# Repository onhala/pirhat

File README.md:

# PIR Sensor Adaption Board

This repository focuses on the development of an adaptation board for the PIR sensor HC-SR501, intended for use in home automation projects. The board adapts the PIR module for integration into a 24V control system.

## Schematic and PCB

The schematic and PCB are located in the `schmatic_pcb` folder in KiCad format.
You can view the schematic online using KiCanvas: [View Schematic](https://kicanvas.org/?github=https%3A%2F%2Fgithub.com%2Fonhala%2Fpirhat%2Ftree%2Fmain%2Fschematic_pcb)

## Cover Manufacturing Files

The manufacturing files for the plastic cover are located in the `cover` folder. They are available in both DWG and PDF formats.

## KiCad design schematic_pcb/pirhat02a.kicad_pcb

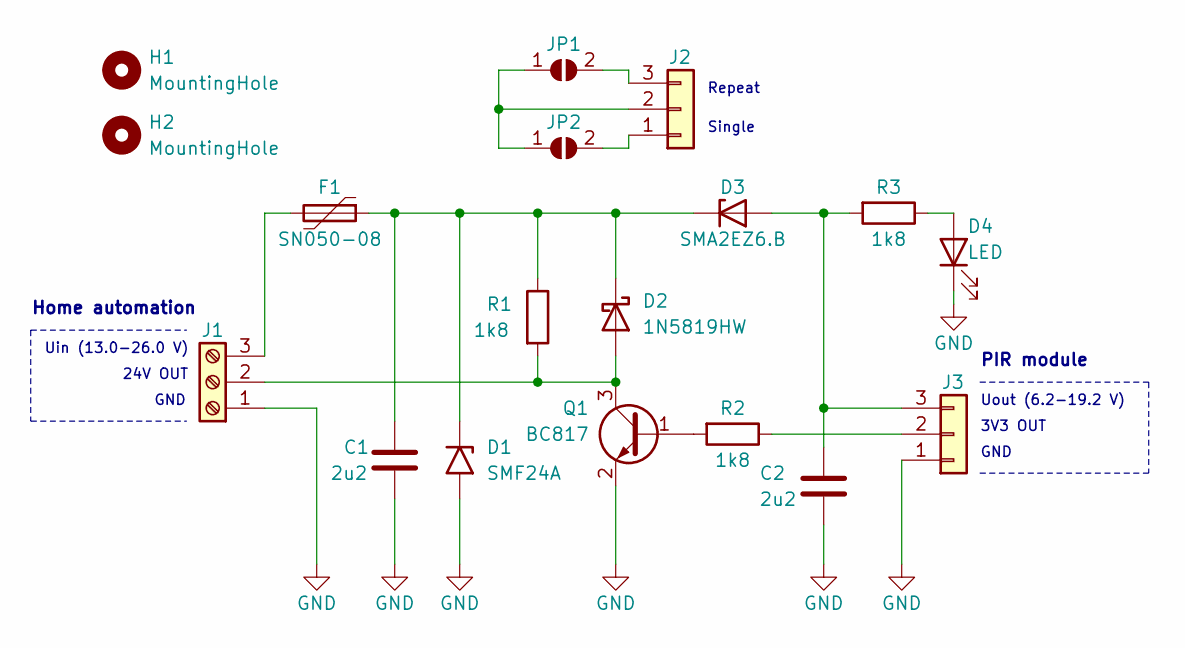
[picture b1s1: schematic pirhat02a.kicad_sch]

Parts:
C1, C2: 2u2; C_1206_3216Metric
D1: SMF24A; D_SMF
D2: 1N5819HW; D_SOD-123
D3: SMA2EZ6.B; D_SMA_Handsoldering
D4: LED; LED_1206_3216Metric_Pad1.42x1.75mm_HandSolder
F1: SN050-08; R_1206_3216Metric_Pad1.30x1.75mm_HandSolder
H1, H2: MountingHole; MountingHole_2.2mm_M2
J1: Screw_Terminal_01x03; TerminalBlock_Phoenix_MKDS-1,5-3-5.08_1x03_P5.08mm_Horizont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
J2, J3: Conn_01x03; PinHeader_1x03_P2.54mm_Vertical
JP1, JP2: SolderJumper_2_Open; SolderJumper-2_P1.3mm_Open_TrianglePad1.0x1.5mm
Q1: BC817; SOT-23_Handsoldering
R1, R2, R3: 1k8; R_1206_3216Metric_Pad1.30x1.75mm_HandSolder

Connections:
GND: C1.2, C2.2, D1.2 (A2), D4.1 (K), J1.1, J3.1, Q1.2 (E)
unnamed: C1.1, D1.1 (A1), D2.1 (K), D3.1 (K), F1.1, R1.1
unnamed: D2.2 (A), J1.2, Q1.3 (C), R1.2
unnamed: C2.1, D3.2 (A), J3.3, R3.2
unnamed: D4.2 (A), R3.1
unnamed: F1.2, J1.3
unnamed: J2.1, JP2.2 (B)
unnamed: J2.2, JP1.1 (A), JP2.1 (A)
unnamed: J2.3, JP1.2 (B)
unnamed: J3.2, R2.1
unnamed: Q1.1 (B), R2.2

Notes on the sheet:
Single
GND
24V OUT
Uout (6.2-19.2 V)
Repeat
Uin (13.0-26.0 V)
PIR module
GND
Home automation
3V3 OUT

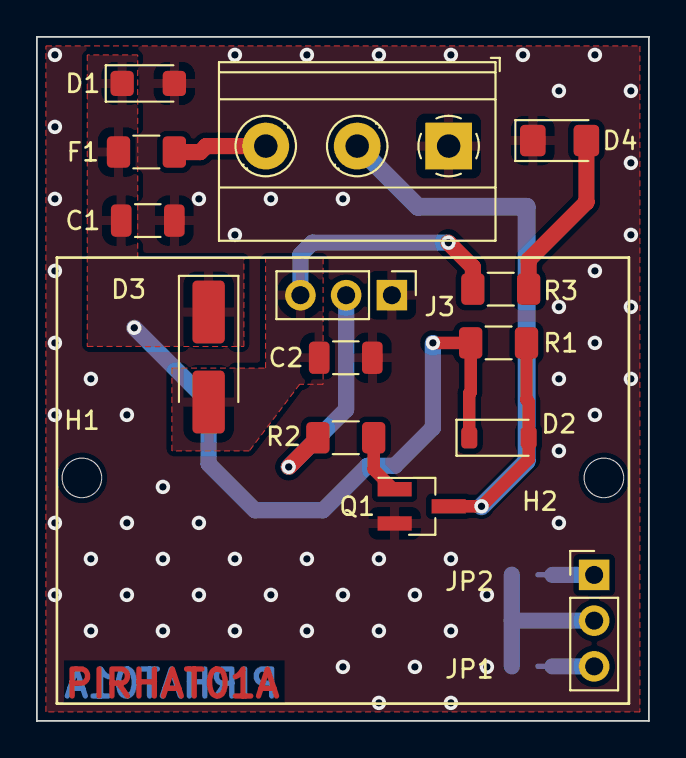
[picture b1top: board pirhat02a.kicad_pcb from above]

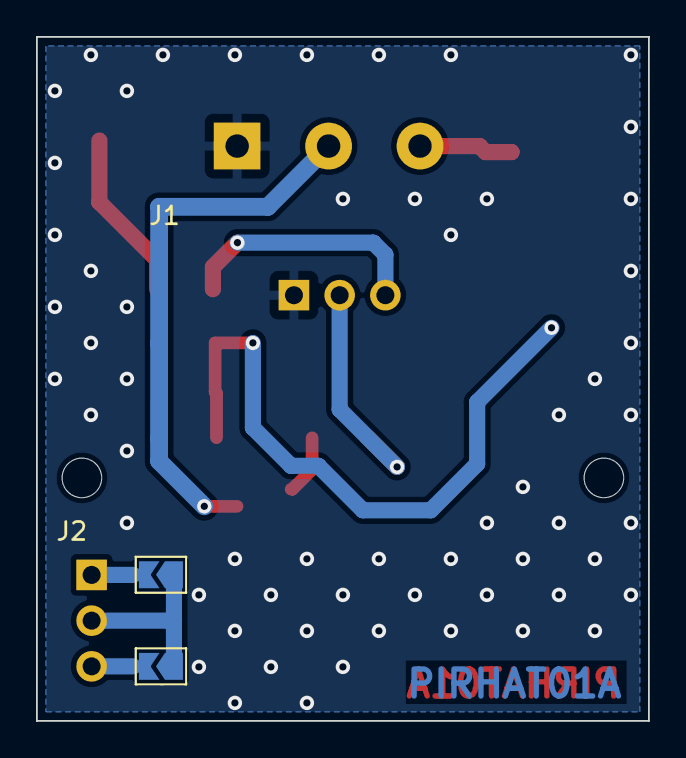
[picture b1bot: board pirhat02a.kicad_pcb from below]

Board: 2 copper layers, 34.0 x 38.0 mm, 18 parts (2 on the bottom side), 11 nets.

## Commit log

2024-12-05 Schematic initial
    Current version of schema and board.
2024-12-05 Update README.md
    intial
2024-12-05 Cover initial
2024-12-05 Update README.md
    added cover information
2024-12-05 Update README.md
    corrected schmatic and board
